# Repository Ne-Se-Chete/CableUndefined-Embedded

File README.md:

# Cable Undefined

> **An AI-powered intelligent breadboard that eliminates physical jumper wires through a dynamically configurable multiplexer matrix.**

Cable Undefined is an embedded hardware and software platform designed to modernize electronics education and rapid prototyping. Instead of manually wiring components on a traditional breadboard, users create circuits digitally while the hardware automatically establishes the required electrical connections.

The project combines custom hardware, a modern web platform, real-time collaboration, and an AI assistant into a single ecosystem focused on making embedded development faster, safer, and significantly more intuitive.

---

# Motivation

Traditional breadboards are one of the biggest obstacles for beginners in electronics.

Even a single misplaced jumper wire may prevent an entire circuit from functioning, making debugging difficult and frustrating. As circuits become larger, cable management quickly becomes the primary challenge instead of the electronics themselves.

Cable Undefined was created to solve exactly this problem.

Instead of physically connecting components with jumper wires, users simply place components inside a virtual breadboard interface while the hardware automatically routes all electrical connections through an intelligent switching matrix.

The result is a significantly cleaner, faster and more beginner-friendly workflow.

---

# Features

## Intelligent Breadboard

- Dynamically configurable connection matrix
- No jumper wires required
- Up to 120 breadboard pins
- Automatic signal routing
- Real-time visualization of active connections

## AI Copilot

Cable Copilot assists users while building circuits by:

- Suggesting component connections
- Detecting wiring mistakes
- Explaining electronic concepts
- Assisting beginners during prototyping

The AI runs locally using **Ollama + Llama3**, meaning no cloud services are required.

---

## Embedded Hardware

The hardware is based around:

- STM32F107VCT6
- 34 × CH446Q analog multiplexers
- ESP32
- CP2102
- WS2812 RGB LEDs
- ADC-based signal analyzer
- Current protection circuitry

The intelligent multiplexer architecture allows dynamic routing of electronic signals while providing visual feedback through individually addressable LEDs. 

---

## Interactive Web Platform

The platform includes:

- Project management
- Interactive breadboard editor
- Component library
- Community gallery
- User profiles
- Real-time collaboration
- Live hardware synchronization

---

# Architecture

```
                Web Interface
                     │
             Next.js Frontend
                     │
              Spring Boot API
                     │
               WebSocket Layer
                     │
             STM32 Controller
                     │
            Multiplexer Matrix
                     │
             Physical Breadboard
```

---

# Technologies

## Hardware

- STM32F107VCT6
- CH446Q Multiplexers
- ESP32
- CP2102
- WS2812 LEDs
- AP22653 Protection IC
- Custom PCB

## Software

- Next.js
- Spring Boot
- Java
- WebSocket
- Keycloak
- Ollama
- Llama
- MongoDB
- PostgreSQL
- R2DBC

---

# Hardware Highlights

- 120 programmable breadboard pins
- Highly optimised mux routing algorithm
- Integrated mini oscilloscope
- DMA-driven LED controller
- Automatic fault protection
- High-speed UART communication
- Local AI integration

---

# Awards

- TUES Fest 2024, Embedded Category
- RoboDays 2024
- ParaIncubator 2024 2x Sponsorship

---

# Timeline

---

# Project Status

> ⚠️ **Project Discontinued**

Development of **Cable Undefined** has been discontinued.

The decision to stop the project was not driven by technical limitations or lack of progress. Instead, development was halted due to external circumstances involving false accusations, persistent defamation, and intellectual property disputes initiated by a former collaborator. These issues created an environment that made continued development and public presentation of the project impractical.

Despite its discontinuation, Cable Undefined remains an important proof of concept demonstrating how hardware, embedded systems, modern web technologies, and local AI can be combined to significantly improve electronics education and rapid prototyping.

The authors:

Yasen Tsvetkov,
Borislav Milanov,
Valeri Todorov,
Tomislav Ivanov,
Emil Momchev,
Simeon Simeonov,
Valentin Asenov

remain proud of the technical achievements accomplished throughout the project's development.

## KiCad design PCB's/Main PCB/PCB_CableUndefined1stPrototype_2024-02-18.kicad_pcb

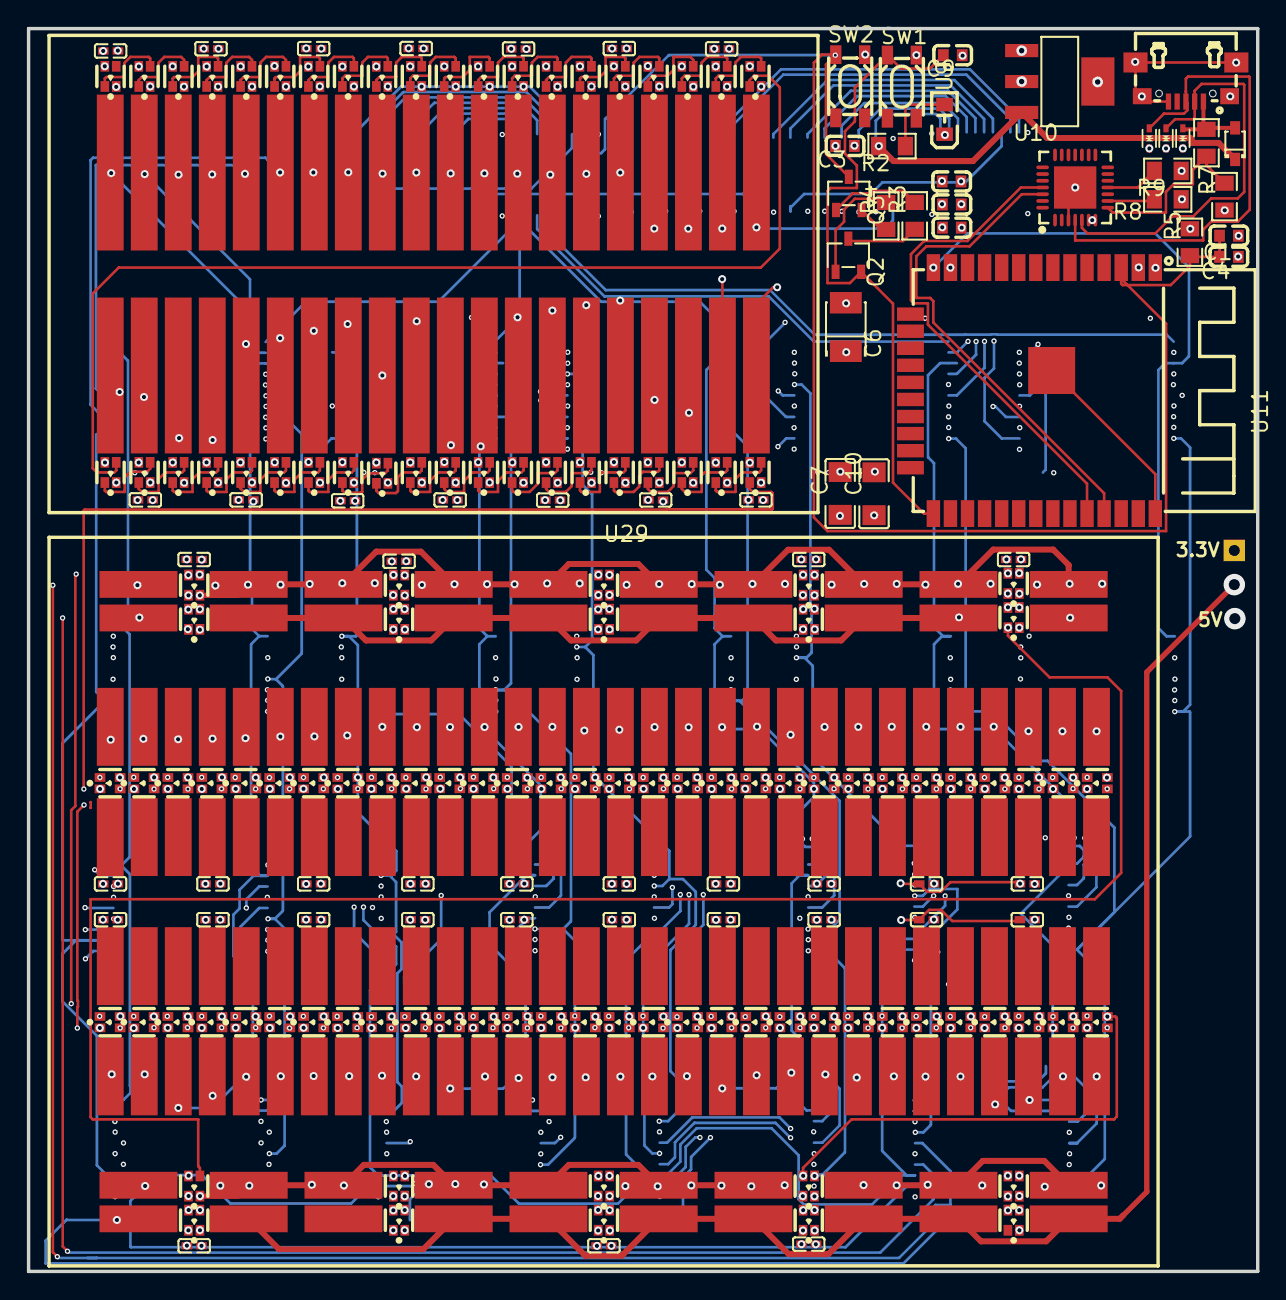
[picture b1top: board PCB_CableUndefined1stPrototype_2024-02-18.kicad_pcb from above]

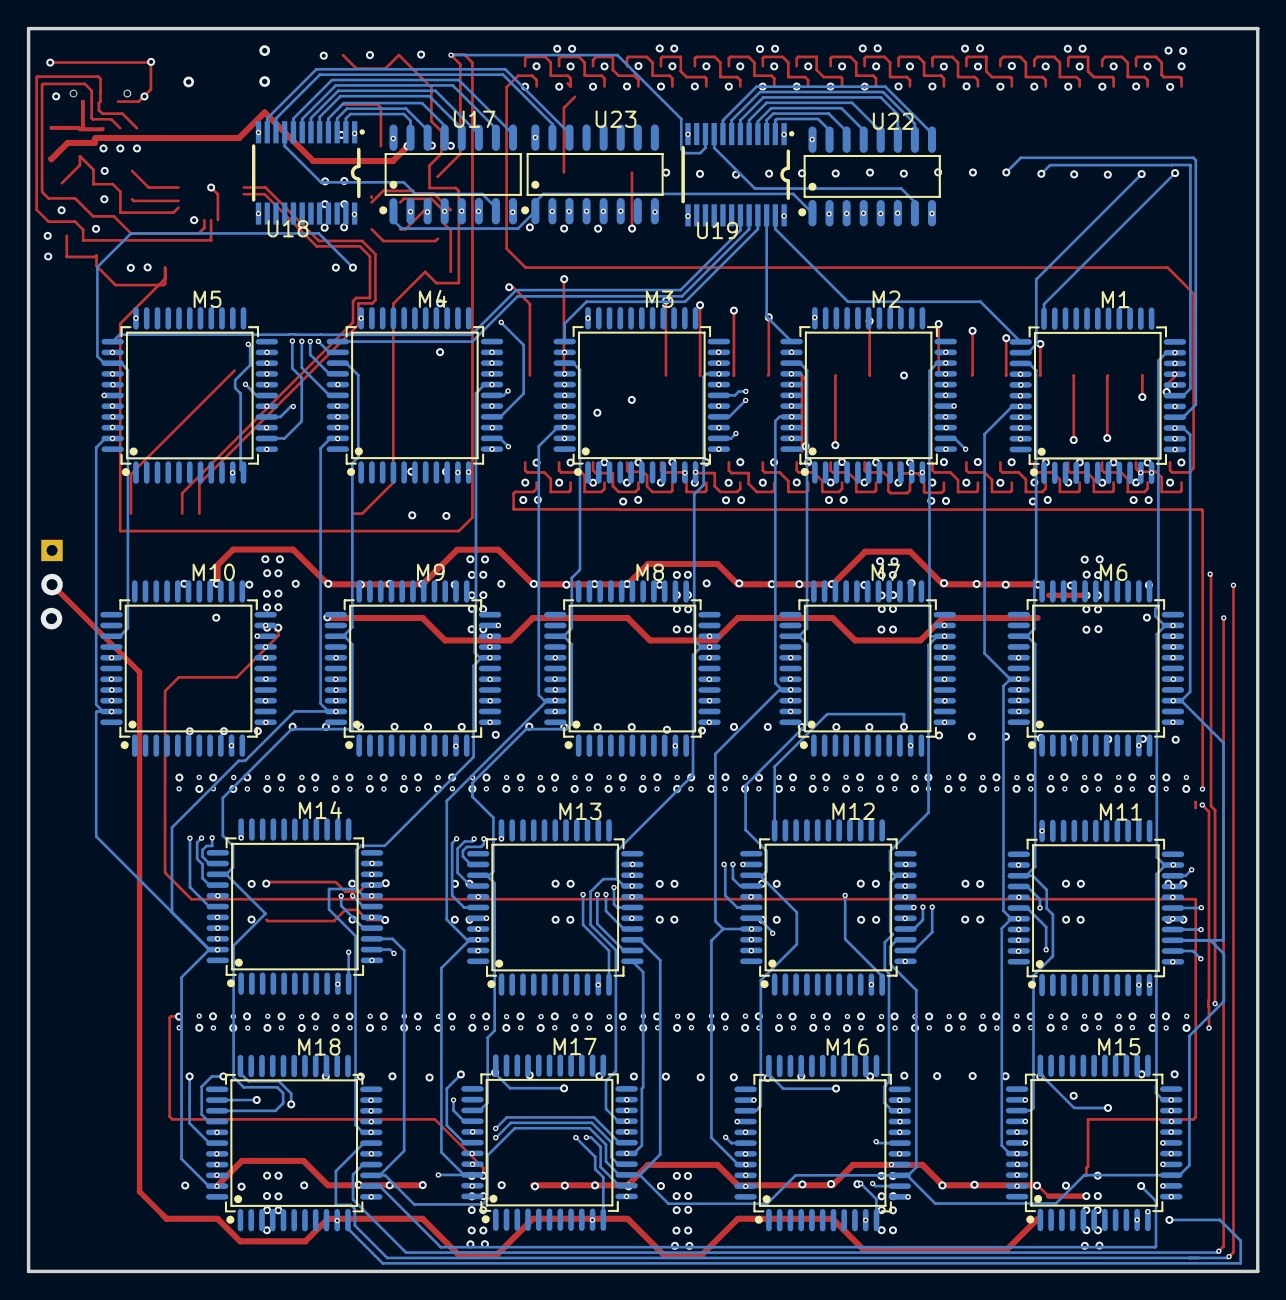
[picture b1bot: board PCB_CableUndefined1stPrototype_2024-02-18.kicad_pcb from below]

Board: 6 copper layers, 91.4 x 92.5 mm, 217 parts (22 on the bottom side), 445 nets.

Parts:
C1, C2, C3, C4, C8, C9, C12: 0.1uF; C0603
C6: 4.7uF; CAP-SMD_L3.5-W2.8
C7, C10: 22uF; C1206
C_LED_1, C_LED_4, C_LED_7, C_LED_10, C_LED_13, C_LED_16, C_LED_19, C_LED_22, C_LED_25, C_LED_28, C_LED_31, C_LED_34, C_LED_37, C_LED_40, C_LED_41, C_LED_44, C_LED_47, C_LED_50, C_LED_53, C_LED_56, C_LED_59, C_LED_62, C_LED_65, C_LED_68, C_LED_71, C_LED_74, C_LED_77, C_LED_80, C_LED_83, C_LED_86, C_LED_89, C_LED_92, C_LED_95, C_LED_98, C_LED_101, C_LED_104, C_LED_107, C_LED_110, C_LED_113, C_LED_116, C_LED_119: 100nF; C0402
D1, D3, D4: LESD5D5.0CT1G; SOD-523_L1.2-W0.8-LS1.6-BI
D2: BAT760; SOD-323_L1.8-W1.3-LS2.5-RD
LED1, LED2, LED3, LED4, LED5, LED6, LED7, LED8, LED9, LED10, LED11, LED12, LED13, LED14, LED15, LED16, LED17, LED18, LED19, LED20, LED21, LED22, LED23, LED24, LED25, LED26, LED27, LED28, LED29, LED30, LED31, LED32, LED33, LED34, LED35, LED36, LED37, LED38, LED39, LED40, LED41, LED42, LED43, LED44, LED45, LED46, LED47, LED48, LED49, LED50, LED51, LED52, LED53, LED54, LED55, LED56, LED57, LED58, LED59, LED60, LED61, LED62, LED63, LED64, LED65, LED66, LED67, LED68, LED69, LED70, LED71, LED72, LED73, LED74, LED75, LED76, LED77, LED78, LED79, LED80, LED81, LED82, LED83, LED84, LED85, LED86, LED87, LED88, LED89, LED90, LED91, LED92, LED93, LED94, LED95, LED96, LED97, LED98, LED99, LED100, LED101, LED102, LED103, LED104, LED105, LED106, LED107, LED108, LED109, LED110, LED111, LED112, LED113, LED114, LED115, LED116, LED117, LED118, LED119, LED120: XL-1615RGBC-WS2812B; LED-SMD_4P-L1.6-W1.5_XL-1615RGBC-WS2812B
M1, M2, M3, M4, M5, M6, M7, M8, M9, M10, M11, M12, M13, M14, M15, M16, M17, M18: CH446Q; LQFP-44_L10.0-W10.0-P0.80-LS12.0-BL
Q2, Q3: MMSS8050-H-TP; SOT-23-3_L2.9-W1.6-P1.90-LS2.8-BR
R2, R8: 2kΩ; R0805
R3, R4, R5, R9: 10kΩ; R0805
R6: 22.1kΩ; R0805
R7: 47.5kΩ; R0805
SW1, SW2: BUTTON-4X3X2.5; SW-SMD_4P-L4.2-W3.2-P2.15-LS5.2
U8: CP2102; QFN-28_L5.0-W5.0-P0.50-TL-EP3.2
U9: 0805 SF-RED; LED0805-RD_RED
U10: AMS1117-1.2; SOT-223-4_L6.5-W3.5-P2.30-LS7.0-BR
U11: ESP-WROOM-32D; COMM-SMD_ESP-WROOM-32D
U12: USB-MICRO-5P; MICRO-USB-SMD_MICRO-USB-A9
U17, U22, U23: SN74LS138D; SOIC-16_L9.9-W3.9-P1.27-LS6.0-BL
U18, U19: 74LVC827APW,118; TSSOP-24_L7.8-W4.4-P0.65-LS6.4-BL
U29: Breadboard400Pin; BREADBOARD 400 POINT
U30: Breadboard 200 pin; BREADBOARD 200 PIN

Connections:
3.3V: C2.2, C6.1, C7.2, C8.2, C10.2, C12.2, R5.2, R8.1, U8.6, U8.7, U10.2, U10.4, U11.2
+5V: C3.2, C_LED_1.1, C_LED_4.1, C_LED_7.1, C_LED_10.1, C_LED_13.1, C_LED_16.1, C_LED_19.1, C_LED_22.1, C_LED_25.1, C_LED_28.1, C_LED_31.1, C_LED_34.1, C_LED_37.1, C_LED_40.1, C_LED_41.1, C_LED_44.1, C_LED_47.1, C_LED_50.1, C_LED_53.1, C_LED_56.1, C_LED_59.1, C_LED_62.1, C_LED_65.1, C_LED_68.1, C_LED_71.1, C_LED_74.1, C_LED_77.1, C_LED_80.1, C_LED_83.1, C_LED_86.1, C_LED_89.1, C_LED_92.1, C_LED_95.1, C_LED_98.1, C_LED_101.1, C_LED_104.1, C_LED_107.1, C_LED_110.1, C_LED_113.1, C_LED_116.1, C_LED_119.1, D2.1, LED1.2, LED2.2, LED3.2, LED4.2, LED5.2, LED6.2, LED7.2, LED8.2, LED9.2, LED10.2, LED11.2, LED12.2, LED13.2, LED14.2, LED15.2, LED16.2, LED17.2, LED18.2, LED19.2, LED20.2, LED21.2, LED22.2, LED23.2, LED24.2, LED25.2, LED26.2, LED27.2, LED28.2, LED29.2, LED30.2, LED31.2, LED32.2, LED33.2, LED34.2, LED35.2, LED36.2, LED37.2, LED38.2, LED39.2, LED40.2, LED41.2, LED42.2, LED43.2, LED44.2, LED45.2, LED46.2, LED47.2, LED48.2, LED49.2, LED50.2, LED51.2, LED52.2, LED53.2, LED54.2, LED55.2, LED56.2, LED57.2, LED58.2, LED59.2, LED60.2, LED61.2, LED62.2, LED63.2, LED64.2, LED65.2, LED66.2, LED67.2, LED68.2, LED69.2, LED70.2, LED71.2, LED72.2, LED73.2, LED74.2, LED75.2, LED76.2, LED77.2, LED78.2, LED79.2, LED80.2, LED81.2, LED82.2, LED83.2, LED84.2, LED85.2, LED86.2, LED87.2, LED88.2, LED89.2, LED90.2, LED91.2, LED92.2, LED93.2, LED94.2, LED95.2, LED96.2, LED97.2, LED98.2, LED99.2, LED100.2, LED101.2, LED102.2, LED103.2, LED104.2, LED105.2, LED106.2, LED107.2, LED108.2, LED109.2, LED110.2, LED111.2, LED112.2, LED113.2, LED114.2, LED115.2, LED116.2, LED117.2, LED118.2, LED119.2, LED120.2, M1.10, M1.38, M2.10, M2.38, M3.10, M3.38, M4.10, M4.38, M5.10, M5.38, M6.10, M6.38, M7.10, M7.38, M8.10, M8.38, M9.10, M9.38, M10.10, M10.38, M11.10, M11.38, M12.10, M12.38, M13.10, M13.38, M14.10, M14.38, M15.10, M15.38, M16.10, M16.38, M17.10, M17.38, M18.10, M18.38, R2.2, U10.3, U17.16, U18.24, U19.24, U22.16, U23.16
ADDR1: U11.16, U17.1, U22.1, U23.1
ADDR2: U11.13, U17.2, U22.2, U23.2
ADDR3: U11.23, U17.3, U22.3, U23.3
ADDR4: U11.27, U17.4, U22.4, U23.5
ADDR5: U11.28, U17.6, U22.5, U23.6
AX0: M1.43, M2.43, M3.43, M4.43, M5.43, M6.43, M7.43, M8.43, M9.43, M10.43, M11.43, M12.43, M13.43, M14.43, M15.43, M16.43, M17.43, M18.43, U11.26
AX1: M1.18, M2.18, M3.18, M4.18, M5.18, M6.18, M7.18, M8.18, M9.18, M10.18, M11.18, M12.18, M13.18, M14.18, M15.18, M16.18, M17.18, M18.18, U11.29
AX2: M1.19, M2.19, M3.19, M4.19, M5.19, M6.19, M7.19, M8.19, M9.19, M10.19, M11.19, M12.19, M13.19, M14.19, M15.19, M16.19, M17.19, M18.19, U11.20
AX3: M1.42, M2.42, M3.42, M4.42, M5.42, M6.42, M7.42, M8.42, M9.42, M10.42, M11.42, M12.42, M13.42, M14.42, M15.42, M16.42, M17.42, M18.42, U11.21
AY0: M1.20, M2.20, M3.20, M4.20, M5.20, M6.20, M7.20, M8.20, M9.20, M10.20, M11.20, M12.20, M13.20, M14.20, M15.20, M16.20, M17.20, M18.20, U11.22
AY1: M1.21, M2.21, M3.21, M4.21, M5.21, M6.21, M7.21, M8.21, M9.21, M10.21, M11.21, M12.21, M13.21, M14.21, M15.21, M16.21, M17.21, M18.21, U11.17
AY2: M1.40, M2.40, M3.40, M4.40, M5.40, M6.40, M7.40, M8.40, M9.40, M10.40, M11.40, M12.40, M13.40, M14.40, M15.40, M16.40, M17.40, M18.40, U11.18
CS/SK_1: M1.34, U19.23
CS/SK_2: M2.34, U19.22
CS/SK_3: M3.34, U19.21
CS/SK_4: M4.34, U19.20
CS/SK_5: M5.34, U19.19
CS/SK_6: M6.34, U19.18
CS/SK_7: M7.34, U19.17
CS/SK_8: M8.34, U19.16
CS/SK_9: M9.34, U18.23
CS/SK_10: M10.34, U18.22
CS/SK_11: M11.34, U18.21
CS/SK_12: M12.34, U18.20
CS/SK_13: M13.34, U18.19
CS/SK_14: M14.34, U18.18
CS/SK_15: M15.34, U18.17
CS/SK_16: M16.34, U18.16
CS/SK_17: M17.34, U18.15
CS/SK_18: M18.34, U18.14
DAT: M1.36, M2.36, M3.36, M4.36, M5.36, M6.36, M7.36, M8.36, M9.36, M10.36, M11.36, M12.36, M13.36, M14.36, M15.36, M16.36, M17.36, M18.36, U11.14
DTR: Q2.3, R3.1
EN: C1.1, C4.1, Q3.3, R5.1, SW2.3, U11.3, U19.10
GND: C1.2, C2.1, C3.1, C4.2, C6.2, C7.1, C8.1, C9.2, C10.1, C12.1, C_LED_1.2, C_LED_4.2, C_LED_7.2, C_LED_10.2, C_LED_13.2, C_LED_16.2, C_LED_19.2, C_LED_22.2, C_LED_25.2, C_LED_28.2, C_LED_31.2, C_LED_34.2, C_LED_37.2, C_LED_40.2, C_LED_41.2, C_LED_44.2, C_LED_47.2, C_LED_50.2, C_LED_53.2, C_LED_56.2, C_LED_59.2, C_LED_62.2, C_LED_65.2, C_LED_68.2, C_LED_71.2, C_LED_74.2, C_LED_77.2, C_LED_80.2, C_LED_83.2, C_LED_86.2, C_LED_89.2, C_LED_92.2, C_LED_95.2, C_LED_98.2, C_LED_101.2, C_LED_104.2, C_LED_107.2, C_LED_110.2, C_LED_113.2, C_LED_116.2, C_LED_119.2, D1.1, D3.1, D4.1, LED1.3, LED2.3, LED3.3, LED4.3, LED5.3, LED6.3, LED7.3, LED8.3, LED9.3, LED10.3, LED11.3, LED12.3, LED13.3, LED14.3, LED15.3, LED16.3, LED17.3, LED18.3, LED19.3, LED20.3, LED21.3, LED22.3, LED23.3, LED24.3, LED25.3, LED26.3, LED27.3, LED28.3, LED29.3, LED30.3, LED31.3, LED32.3, LED33.3, LED34.3, LED35.3, LED36.3, LED37.3, LED38.3, LED39.3, LED40.3, LED41.3, LED42.3, LED43.3, LED44.3, LED45.3, LED46.3, LED47.3, LED48.3, LED49.3, LED50.3, LED51.3, LED52.3, LED53.3, LED54.3, LED55.3, LED56.3, LED57.3, LED58.3, LED59.3, LED60.3, LED61.3, LED62.3, LED63.3, LED64.3, LED65.3, LED66.3, LED67.3, LED68.3, LED69.3, LED70.3, LED71.3, LED72.3, LED73.3, LED74.3, LED75.3, LED76.3, LED77.3, LED78.3, LED79.3, LED80.3, LED81.3, LED82.3, LED83.3, LED84.3, LED85.3, LED86.3, LED87.3, LED88.3, LED89.3, LED90.3, LED91.3, LED92.3, LED93.3, LED94.3, LED95.3, LED96.3, LED97.3, LED98.3, LED99.3, LED100.3, LED101.3, LED102.3, LED103.3, LED104.3, LED105.3, LED106.3, LED107.3, LED108.3, LED109.3, LED110.3, LED111.3, LED112.3, LED113.3, LED114.3, LED115.3, LED116.3, LED117.3, LED118.3, LED119.3, LED120.3, M1.12, M1.16, M2.12, M2.16, M3.12, M3.16, M4.12, M4.16, M5.12, M5.16, M6.12, M6.16, M7.12, M7.16, M8.12, M8.16, M9.12, M9.16, M10.12, M10.16, M11.12, M11.16, M12.12, M12.16, M13.12, M13.16, M14.12, M14.16, M15.12, M15.16, M16.12, M16.16, M17.12, M17.16, M18.12, M18.16, R7.1, R9.1, SW1.1, SW2.1, U8.3, U8.29, U9.1, U10.1, U11.1, U12.5, U12.6, U12.7, U12.8, U12.9, U17.5, U17.8, U18.1, U18.12, U18.13, U19.1, U19.12, U19.13, U22.6, U22.8, U23.4, U23.8, U29.NC
IO0: C9.1, Q2.2, SW1.3, U11.25
LED1_1: LED1.1, LED2.4
LED2_1: LED2.1, LED3.4
LED3_1: LED3.1, LED4.4
LED4_1: LED4.1, LED5.4
LED5_1: LED5.1, LED6.4
LED6_1: LED6.1, LED7.4
LED7_1: LED7.1, LED8.4
LED8_1: LED8.1, LED9.4
LED9_1: LED9.1, LED10.4
LED10_1: LED10.1, LED11.4
LED11_1: LED11.1, LED12.4
LED12_1: LED12.1, LED13.4
LED13_1: LED13.1, LED14.4
LED14_1: LED14.1, LED15.4
LED15_1: LED15.1, LED16.4
LED16_1: LED16.1, LED17.4
LED17_1: LED17.1, LED18.4
LED18_1: LED18.1, LED19.4
LED19_1: LED19.1, LED20.4
LED20_1: LED20.1, LED21.4
LED21_1: LED21.1, LED22.4
LED22_1: LED22.1, LED23.4
LED23_1: LED23.1, LED24.4
LED24_1: LED24.1, LED25.4
LED25_1: LED25.1, LED26.4
LED26_1: LED26.1, LED27.4
LED27_1: LED27.1, LED28.4
LED28_1: LED28.1, LED29.4
LED29_1: LED29.1, LED30.4
LED30_1: LED30.1, LED31.4
LED31_1: LED31.1, LED32.4
LED32_1: LED32.1, LED33.4
LED33_1: LED33.1, LED34.4
LED34_1: LED34.1, LED35.4
LED35_1: LED35.1, LED36.4
LED36_1: LED36.1, LED37.4
LED37_1: LED37.1, LED38.4
LED38_1: LED38.1, LED39.4
LED39_1: LED39.1, LED40.4
LED40_1: LED40.1, LED41.4
LED41_1: LED41.1, LED42.4
LED42_1: LED42.1, LED43.4
LED43_1: LED43.1, LED44.4
LED44_1: LED44.1, LED45.4
LED45_1: LED45.1, LED46.4
LED46_1: LED46.1, LED47.4
LED47_1: LED47.1, LED48.4
LED48_1: LED48.1, LED49.4
LED49_1: LED49.1, LED50.4
LED50_1: LED50.1, LED51.4
LED51_1: LED51.1, LED52.4
LED52_1: LED52.1, LED53.4
LED53_1: LED53.1, LED54.4
LED54_1: LED54.1, LED55.4
LED55_1: LED55.1, LED56.4
LED56_1: LED56.1, LED57.4
LED57_1: LED57.1, LED58.4
LED58_1: LED58.1, LED59.4
LED59_1: LED59.1, LED60.4
LED60_1: LED60.1, LED61.4
LED62_4: LED61.1, LED62.4
LED63_4: LED62.1, LED63.4
LED64_4: LED63.1, LED64.4
LED65_4: LED64.1, LED65.4
LED66_4: LED65.1, LED66.4
LED67_4: LED66.1, LED67.4
LED68_4: LED67.1, LED68.4
LED69_4: LED68.1, LED69.4
LED70_4: LED69.1, LED70.4
LED71_4: LED70.1, LED71.4
LED72_4: LED71.1, LED72.4
LED73_4: LED72.1, LED73.4
LED74_4: LED73.1, LED74.4
LED75_4: LED74.1, LED75.4
LED76_4: LED75.1, LED76.4
LED77_4: LED76.1, LED77.4
LED78_4: LED77.1, LED78.4
LED79_4: LED78.1, LED79.4
LED80_4: LED79.1, LED80.4
LED81_4: LED80.1, LED81.4
LED82_4: LED81.1, LED82.4
LED83_4: LED82.1, LED83.4
LED84_4: LED83.1, LED84.4
LED85_4: LED84.1, LED85.4
LED86_4: LED85.1, LED86.4
LED87_4: LED86.1, LED87.4
LED88_4: LED87.1, LED88.4
LED89_4: LED88.1, LED89.4
LED90_4: LED89.1, LED90.4
LED91_4: LED90.1, LED91.4
LED92_4: LED91.1, LED92.4
LED93_4: LED92.1, LED93.4
LED94_4: LED93.1, LED94.4
LED95_4: LED94.1, LED95.4
LED96_4: LED95.1, LED96.4
LED97_4: LED96.1, LED97.4
LED98_4: LED97.1, LED98.4
LED99_4: LED98.1, LED99.4
LED100_1: LED100.1, LED101.4
LED100_4: LED99.1, LED100.4
LED102_4: LED101.1, LED102.4
LED103_1: LED103.1, LED104.4
LED103_4: LED102.1, LED103.4
LED104_1: LED104.1, LED105.4
LED105_1: LED105.1, LED106.4
LED106_1: LED106.1, LED107.4
LED107_1: LED107.1, LED108.4
LED108_1: LED108.1, LED109.4
LED109_1: LED109.1, LED110.4
LED110_1: LED110.1, LED111.4
LED111_1: LED111.1, LED112.4
LED112_1: LED112.1, LED113.4
LED113_1: LED113.1, LED114.4
LED114_1: LED114.1, LED115.4
LED115_1: LED115.1, LED116.4
LED116_1: LED116.1, LED117.4
LED117_1: LED117.1, LED118.4
LED118_1: LED118.1, LED119.4
LED119_1: LED119.1, LED120.4
M6_1: M6.1, M7.1
M6_2: M6.2, M8.1
M6_24: M6.24, M10.2
M9_1: M7.2, M9.1
M9_2: M8.2, M9.2
M10_1: M7.24, M10.1
M10_24: M8.24, M10.24
M10_25: M9.24, M10.25
MAIN_BRBOARD_1: M11.33, U29.1
MAIN_BRBOARD_2: M11.35, U29.2
MAIN_BRBOARD_3: M11.37, U29.3
MAIN_BRBOARD_4: M11.39, U29.4
MAIN_BRBOARD_5: M11.17, U29.5
MAIN_BRBOARD_6: M11.15, U29.6
MAIN_BRBOARD_7: M11.13, U29.7
MAIN_BRBOARD_8: M11.11, U29.8
MAIN_BRBOARD_9: M12.33, U29.9
MAIN_BRBOARD_10: M12.35, U29.10
MAIN_BRBOARD_11: M12.37, U29.11
MAIN_BRBOARD_12: M12.39, U29.12
MAIN_BRBOARD_13: M12.17, U29.13
MAIN_BRBOARD_14: M12.15, U29.14
MAIN_BRBOARD_15: M12.13, U29.15
MAIN_BRBOARD_16: M12.11, U29.16
MAIN_BRBOARD_17: M13.33, U29.17
MAIN_BRBOARD_18: M13.35, U29.18
MAIN_BRBOARD_19: M13.37, U29.19
MAIN_BRBOARD_20: M13.39, U29.20
MAIN_BRBOARD_21: M13.17, U29.21
MAIN_BRBOARD_22: M13.15, U29.22
MAIN_BRBOARD_23: M13.13, U29.23
MAIN_BRBOARD_24: M13.11, U29.24
MAIN_BRBOARD_25: M14.33, U29.25
MAIN_BRBOARD_26: M14.35, U29.26
MAIN_BRBOARD_27: M14.37, U29.27
MAIN_BRBOARD_28: M14.39, U29.28
MAIN_BRBOARD_29: M14.17, U29.29
MAIN_BRBOARD_30: M14.15, U29.30
MAIN_BRBOARD_31: M14.13, U29.31
MAIN_BRBOARD_32: M14.11, U29.32
MAIN_BRBOARD_33: M15.33, U29.33
MAIN_BRBOARD_34: M15.35, U29.34
MAIN_BRBOARD_35: M15.37, U29.35
MAIN_BRBOARD_36: M15.39, U29.36
MAIN_BRBOARD_37: M15.17, U29.37
MAIN_BRBOARD_38: M15.15, U29.38
MAIN_BRBOARD_39: M15.13, U29.39
MAIN_BRBOARD_40: M15.11, U29.40
MAIN_BRBOARD_41: M16.33, U29.41
MAIN_BRBOARD_42: M16.35, U29.42
MAIN_BRBOARD_43: M16.37, U29.43
MAIN_BRBOARD_44: M16.39, U29.44
MAIN_BRBOARD_45: M16.17, U29.45
MAIN_BRBOARD_46: M16.15, U29.46
MAIN_BRBOARD_47: M16.13, U29.47
MAIN_BRBOARD_48: M16.11, U29.48
MAIN_BRBOARD_49: M17.33, U29.49
MAIN_BRBOARD_50: M17.35, U29.50
MAIN_BRBOARD_51: M17.37, U29.51
MAIN_BRBOARD_52: M17.39, U29.52
MAIN_BRBOARD_53: M17.17, U29.53
MAIN_BRBOARD_54: M17.15, U29.54
MAIN_BRBOARD_55: M17.13, U29.55
MAIN_BRBOARD_56: M17.11, U29.56
MAIN_BRBOARD_57: M18.33, U29.57
MAIN_BRBOARD_58: M18.35, U29.58
MAIN_BRBOARD_59: M18.37, U29.59
MAIN_BRBOARD_60: M18.39, U29.60
MAIN_BRBOARD_61: M18.17, U29.61
MAIN_BRBOARD_62: M18.15, U29.62
MAIN_BRBOARD_63: M18.13, U29.63
MAIN_BRBOARD_64: M18.11, U29.64
MCU_BRBOARD_1: M1.33, U30.1
MCU_BRBOARD_2: M1.35, U30.2
MCU_BRBOARD_3: M1.37, U30.3
MCU_BRBOARD_4: M1.39, U30.4
MCU_BRBOARD_5: M1.17, U30.5
MCU_BRBOARD_6: M1.15, U30.6
MCU_BRBOARD_7: M1.13, U30.7
MCU_BRBOARD_8: M1.11, U30.8
MCU_BRBOARD_9: M2.33, U30.9
MCU_BRBOARD_10: M2.35, U30.10
MCU_BRBOARD_11: M2.37, U30.11
MCU_BRBOARD_12: M2.39, U30.12
MCU_BRBOARD_13: M2.17, U30.13
MCU_BRBOARD_14: M2.15, U30.14
MCU_BRBOARD_15: M2.13, U30.15
MCU_BRBOARD_16: M2.11, U30.16
MCU_BRBOARD_17: M3.33, U30.17
MCU_BRBOARD_18: M3.35, U30.18
MCU_BRBOARD_19: M3.37, U30.19
MCU_BRBOARD_20: M3.39, U30.20
MCU_BRBOARD_21: M3.17, U30.21
MCU_BRBOARD_22: M3.15, U30.22
MCU_BRBOARD_23: M3.13, U30.23
MCU_BRBOARD_24: M3.11, U30.24
MCU_BRBOARD_25: M4.33, U30.25
MCU_BRBOARD_26: M4.35, U30.26
MCU_BRBOARD_27: M4.37, U30.27
MCU_BRBOARD_28: M4.39, U30.28
MCU_BRBOARD_29: M4.17, U30.29
MCU_BRBOARD_30: M4.15, U30.30
MCU_BRBOARD_31: M4.13, U30.31
MCU_BRBOARD_32: M4.11, U30.32
MCU_BRBOARD_33: M5.33, U30.33
MCU_BRBOARD_34: M5.35, U30.34
MCU_BRBOARD_35: M5.37, U30.35
MCU_BRBOARD_36: M5.39, U30.36
MCU_BRBOARD_37: M5.17, U30.37
MCU_BRBOARD_38: M5.15, U30.38
MCU_BRBOARD_39: M5.13, U30.39
MCU_BRBOARD_40: M5.11, U30.40
Q3_1: Q3.1, R3.2
R2_1: R2.1, U9.2
R4_2: Q2.1, R4.2
RST: M1.41, M2.41, M3.41, M4.41, M5.41, M6.41, M7.41, M8.41, M9.41, M10.41, M11.41, M12.41, M13.41, M14.41, M15.41, M16.41, M17.41, M18.41, U19.15
RTS: Q3.2, R4.1
RXD: U8.26, U11.35
STB: M1.14, M2.14, M3.14, M4.14, M5.14, M6.14, M7.14, M8.14, M9.14, M10.14, M11.14, M12.14, M13.14, M14.14, M15.14, M16.14, M17.14, M18.14, U11.19
TXD: U8.25, U11.34
U8_8: R6.2, R7.2, U8.8
U8_9: R8.2, U8.9
U8_11: R9.2, U8.11
U11_38: U11.38, U11.39
USB_DN: D3.2, U8.5, U12.2
USB_DP: D1.2, U8.4, U12.3
VBUS: D2.2, D4.2, R6.1, U12.1
X0_1: M1.31, M11.31
X0_2: M2.31, M11.30
X0_3: M3.31, M11.29
X0_4: M4.31, M11.28
X0_5: M5.31, M11.27
X0_6: M6.31, M11.26
X0_7: M7.31, M11.3
X0_8: M8.31, M11.4
X0_9: M9.31, M11.5
X0_10: M10.31, M11.6
X1_1: M1.30, M12.31
X1_2: M2.30, M12.30
X1_3: M3.30, M12.29
X1_4: M4.30, M12.28
X1_5: M5.30, M12.27
X1_6: M6.30, M12.26
X1_7: M7.30, M12.3
X1_8: M8.30, M12.4
X1_9: M9.30, M12.5
X1_10: M10.30, M12.6
X2_1: M1.29, M13.31
X2_2: M2.29, M13.30
X2_3: M3.29, M13.29
X2_4: M4.29, M13.28
X2_5: M5.29, M13.27
X2_6: M6.29, M13.26
X2_7: M7.29, M13.3
X2_8: M8.29, M13.4
X2_9: M9.29, M13.5
X2_10: M10.29, M13.6
X3_1: M1.28, M14.31
X3_2: M2.28, M14.30
X3_3: M3.28, M14.29
X3_4: M4.28, M14.28
X3_5: M5.28, M14.27
X3_6: M6.28, M14.26
X3_7: M7.28, M14.3
X3_8: M8.28, M14.4
X3_9: M9.28, M14.5
X3_10: M10.28, M14.6
X4_1: M1.27, M15.31
X4_2: M2.27, M15.30
X4_3: M3.27, M15.29
X4_4: M4.27, M15.28
X4_5: M5.27, M15.27
X4_6: M6.27, M15.26
X4_7: M7.27, M15.3
X4_8: M8.27, M15.4
X4_9: M9.27, M15.5
X4_10: M10.27, M15.6
X5_1: M1.26, M16.31
X5_2: M2.26, M16.30
X5_3: M3.26, M16.29
X5_4: M4.26, M16.28
X5_5: M5.26, M16.27
X5_6: M6.26, M16.26
X5_7: M7.26, M16.3
X5_8: M8.26, M16.4
X5_9: M9.26, M16.5
X5_10: M10.26, M16.6
X6_1: M1.3, M17.31
X6_2: M2.3, M17.30
X6_3: M3.3, M17.29
X6_4: M4.3, M17.28
X6_5: M5.3, M17.27
X6_6: M6.3, M17.26
X6_7: M7.3, M17.3
X6_8: M8.3, M17.4
X6_9: M9.3, M17.5
X6_10: M10.3, M17.6
X7_1: M1.4, M18.31
X7_2: M2.4, M18.30
X7_3: M3.4, M18.29
X7_4: M4.4, M18.28
X7_5: M5.4, M18.27
X7_6: M6.4, M18.26
X7_7: M7.4, M18.3
X7_8: M8.4, M18.4
X7_9: M9.4, M18.5
X7_10: M10.4, M18.6
X8_1: M1.5, M6.33
X8_2: M2.5, M6.35
X8_3: M3.5, M6.37
X8_4: M4.5, M6.39
X8_5: M5.5, M6.17
X8_6: M6.5, M11.7
X8_7: M7.5, M12.25
X8_8: M8.5, M14.8
X8_9: M9.5, M16.7
X8_10: M10.5, M17.25
X9_1: M1.6, M7.33
X9_2: M2.6, M7.35
X9_3: M3.6, M7.37
X9_4: M4.6, M7.39
X9_5: M5.6, M7.17
X9_6: M6.6, M11.8
X9_7: M7.6, M13.7
X9_8: M8.6, M14.25
X9_9: M9.6, M16.8
X9_10: M10.6, M18.7
X10_1: M1.7, M8.33
X10_2: M2.7, M8.35
X10_3: M3.7, M8.37
X10_4: M4.7, M8.39
X10_5: M5.7, M8.17
X10_6: M6.7, M11.25
X10_7: M7.7, M13.8
X10_8: M8.7, M15.7
X10_9: M9.7, M16.25
X10_10: M10.7, M18.8
X11_1: M1.8, M9.33
X11_2: M2.8, M9.35
X11_3: M3.8, M9.37
X11_4: M4.8, M9.39
X11_5: M5.8, M9.17
X11_6: M6.8, M12.7
X11_7: M7.8, M13.25
X11_8: M8.8, M15.8
X11_9: M9.8, M17.7
X11_10: M10.8, M18.25
X12_1: M1.25, M10.33
X12_2: M2.25, M10.35
X12_3: M3.25, M10.37
X12_4: M4.25, M10.39
X12_5: M5.25, M10.17
X12_6: M6.25, M12.8
X12_7: M7.25, M14.7
X12_8: M8.25, M15.25
X12_9: M9.25, M17.8
X13_1: M1.24, M6.15
X13_2: M2.24, M7.15
X13_3: M3.24, M8.15
X13_4: M4.24, M9.15
X13_5: M5.24, M10.15
X14_1: M1.1, M6.13
X14_2: M2.1, M7.13
X14_3: M3.1, M8.13
X14_4: M4.1, M9.13
X14_5: M5.1, M10.13
X15_1: M1.2, M6.11
X15_2: M2.2, M7.11
X15_3: M3.2, M8.11
X15_4: M4.2, M9.11
X15_5: M5.2, M10.11
Y0_1: U19.2, U22.15
Y0_2: U17.15, U18.2
Y0_3: U18.10, U23.15
Y1_1: U19.3, U22.14
Y1_2: U17.14, U18.3
Y1_3: U18.11, U23.14
Y2_1: U19.4, U22.13
Y2_2: U17.13, U18.4
Y3_1: U19.5, U22.12
Y3_2: U17.12, U18.5
Y4_1: U19.6, U22.11
Y4_2: U17.11, U18.6
Y5_1: U19.7, U22.10
Y5_2: U17.10, U18.7
Y6_1: U19.8, U22.9
Y6_2: U17.9, U18.8
Y7_1: U19.9, U22.7
Y7_2: U17.7, U18.9

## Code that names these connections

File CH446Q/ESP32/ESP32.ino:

#include "Arduino.h"

#define STB_PIN 34
#define DAT_PIN 35

#define AY0_PIN 4
#define AY1_PIN 2
#define AY2_PIN 15

#define AX0_PIN 18
#define AX1_PIN 5
#define AX2_PIN 17
#define AX3_PIN 16

#define ADDR0_PIN 19
#define ADDR1_PIN 21
#define ADDR2_PIN 22
#define ADDR3_PIN 23

#define MAX_ADDRESS 15
#define MAX_AX 15
#define MAX_AY 7

void setupPins() {
  pinMode(STB_PIN, OUTPUT);
  pinMode(DAT_PIN, OUTPUT);

  pinMode(AY0_PIN, OUTPUT);
  pinMode(AY1_PIN, OUTPUT);
  pinMode(AY2_PIN, OUTPUT);

  pinMode(AX0_PIN, OUTPUT);
  pinMode(AX1_PIN, OUTPUT);
  pinMode(AX2_PIN, OUTPUT);
  pinMode(AX3_PIN, OUTPUT);

  pinMode(ADDR0_PIN, OUTPUT);
  pinMode(ADDR1_PIN, OUTPUT);
  pinMode(ADDR2_PIN, OUTPUT);
  pinMode(ADDR3_PIN, OUTPUT);
}

int setConnection(uint8_t addr, uint8_t AX, uint8_t AY, bool mode) {
  if (addr > MAX_ADDRESS || AX > MAX_AX || AY > MAX_AY) {
    return -1;
  }

  // Set ADDR_PORT bits using digitalWrite
  digitalWrite(ADDR0_PIN, 1);
  digitalWrite(ADDR1_PIN, 1);
  digitalWrite(ADDR2_PIN, 1);
  digitalWrite(ADDR3_PIN, 0);

  // Set AX_PORT bits using digitalWrite
  digitalWrite(AX0_PIN, 0);
  digitalWrite(AX1_PIN, 0);
  digitalWrite(AX2_PIN, 0);
  digitalWrite(AX3_PIN, 0);

  // Set AY_PORT bits using digitalWrite
  digitalWrite(AY0_PIN, 0);
  digitalWrite(AY1_PIN, 0);
  digitalWrite(AY2_PIN, 0);

  digitalWrite(DAT_PIN, mode);

  digitalWrite(STB_PIN, HIGH);  // Set STB high

  delayMicroseconds(2);

  digitalWrite(STB_PIN, LOW);  // Set STB low

  return 1;
}

void setup() {
  setupPins();
  setConnection(0b1111, 1, 1, true);
}

void loop() {
  // Your loop code here
}

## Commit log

2023-10-16 CH446Q WORKS!
2023-11-02 Pico works on linux
2023-11-02 init a bit more stuff
2023-11-03 FIX CPP PROPERTIES
2023-11-25 CH446Q REACHES 100C?!!?!?!
2024-01-16 small bug CH446Q.ino
2024-01-17 init some ESP stuff + datasheet
2024-01-17 commit predi da se vidq s garistov
2024-01-20 ESP32 AND RASPBERRY PI PICO WORKS!!!
2024-01-29 init algorithm for pathfindingthrough MUX
2024-01-29 init main multiplexer code classes
2024-01-30 add bidirectional connection check
2024-01-30 baca
2024-01-30 add breadboard
2024-02-21 add init for graph
2024-02-22 add code for DFS graph
2024-02-23 small changes
2024-02-24 add nidirectional connections for MUX1 and MUX2
2024-02-24 Add all bydirectional connection nodes for MUX3 and MUX4
2024-02-24 add bydirectional connection for MUX5
2024-02-24 add bydirectional connections for MUX6 MUX7
2024-02-24 add bydirectional connections for MUX8 MUX9 MUX10
2024-02-24 all bydirectional connections for MUX11 -> MUX18
2024-02-24 add bydirectional connections between helper MUXes
2024-02-25 fix bug with main_breadboard and mcu_breadboard indexes
2024-02-25 add loop to add all edges between X and y nodes
2024-02-25 add edges for MUX1 MUX2 MUX3
2024-02-25 add edges for MUX4 and MUX5
2024-02-25 add conections for MUX6 MUX7 MUX8
2024-02-25 add connections for MUX9 and MUX10
2024-02-25 add edges for MUX10 -> MUX15
2024-02-25 add edges for MUX18
2024-02-26 add dfs with used paths
2024-02-26 add BFS search and print Device from index
2024-02-27 add bfs used pins check
2024-02-27 add path_request function
2024-02-28 Add PCB's
2024-03-01 add printing functions for founded paths
2024-03-03 add printing founded paths to txt file
2024-03-09 add mini path finding algo
2024-03-09 add working pathfinding for mini scheme
2024-03-21 ws1228b
2024-03-27 fix graph edges bu pathfiding doesnt work.
2024-03-27 pathfinding DOESNT WOKR AT ALL
2024-03-28 add code for printing SetConections
2024-03-29 replace unordered_map and unordered_set with simple arrays
2024-03-29 remove checkBidirectional and printConnections. Removed dynamic_cast and virtual. Working pathfiding
2024-03-30 removed printing to file and to_string
2024-04-02 add to_string and removed writing in file
2024-04-16 demonza para
2024-04-16 fix merge sht
2024-04-16 fix a bit dirs
2024-04-16 tuesfestdemo init
2024-04-16 NEEDS PARSE FIXING
2024-04-17 EVERYTHING WORKS
2024-05-01 python demo connections work, to ad UI
2024-05-03 most of the ui wokrs
2024-05-04 connections work, have to fix colored ui
2024-05-07 comit shoto zabrawih
2024-05-07 to fix tmr, doesnt work
2024-05-08 connections override y0, y0
2024-05-08 BREAK DOESNT BREAK WTF
2024-05-08 kashlqm
2024-05-08 MAYBE WORKS TEST TMR IN OOP
2024-05-09 EVEYTHING FOR 13 MAY WORKS
2024-05-10 add some pcb files
2024-05-11 FRONTEND add: sidebar with search capabilities
2024-05-11 frontend fix: sidebar search now works properly
2024-05-11 FRONTENT add: when a button is clicked a new window is opened with the data init
2024-05-11 FRONTEND add: working gpt integration
2024-05-11 FRONTEND fix: sidebar rename
2024-09-16 this works rn
2024-09-16 added MUX class, another 1 mux dead tho
2024-09-17 setting up mux pins (adding schematic in code basically)
2024-09-18 finds pins, remove tracks doesnt work
2024-09-18 main track control
2024-09-18 setting tracks works, to be released
2024-09-18 releasing works
2024-09-18 set + remove works like a charm with algorithm
2024-09-18 fix ay and ax calculation in setconnection
2024-09-19 f446ze update
2024-09-20 RABOTI BE, RAZGELE :)))))))
2024-09-20 minor fix
2024-09-20 minor fixes
2024-09-21 WORKS WITH EMO 7:53
2024-09-21 add CLR fucntion
2025-02-19 add base test code for STM32HAL MUX testing with C
2025-02-19 name fix
2025-02-19 name fix 2
2025-02-22 add partial algorithm for pathfinding
2025-02-23 routing works
2025-02-27 Full working pathfinding +UART receive from PC (CP2102)
2025-03-03 UART works with ESP and CP2102, with interrupts
2025-03-08 ADC sig analyzer works
2025-03-09 fault works!, to look at tim6 and leds (tim1)
2025-03-15 feat: adding pwm tim2 ch1 pa15
2025-03-15 feat: light up first row
2025-03-18 WORKING LEDS TF DMA IS SHIT
2025-03-18 add removing leds and CLR for leds is tested
2025-03-18 fix so Route 1-5, 5-10, Remove 5-10, removes only LED 10 + CLR FIXES
2025-03-25 restructure repo + fixed strange 2 route connection bug accidental removal + fixed needles increment of maintrack and muxusage vars on repetative commands
2025-03-25 add PCB's and schematics
2025-03-25 remove unnecesaary files
2025-03-25 fix leds not turrning off on redundant same connections
2025-03-25 add DMA for ADC, made UART faster 1700us per sample, because of printf. Have to fix
2025-03-25 Signal analyzer ~80us on 1 signal = ~12khz, added ADC turning on optimisation, sending only on 1 uart, ad python test file
2025-04-08 this works esp and cp2102 both
2025-04-08 start code for digital signal ana,yzer, till now works fine
2025-04-08 add NOT WORKIGN LOGIC FOR DIGITAL SIG ANALYZER
2025-04-08 add sampling time and digital to Adc and bak works, digital doesnt measure properly
2025-04-24 final commit, closing Cable Undefined V3 project, greetings
2025-04-24 add readme, although project ist inactive
2025-04-24 update readme images
